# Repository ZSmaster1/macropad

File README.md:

# Macropad

This macropad has 9 keys, an OLED display, a rotary encoder, and 20 individually adressable LEDs for an underglow effect.

## Features
* Two piece PLA case (no screws or heatset inserts necessary!)
* 128x32 OLED display
* EC11 rotary encoder
* 9 keys arranged in a 3x3 matrix
* 20 SK6812MINI-E indvidually adressable LEDs for underglow effects
* Supports QMK, KMK, and more

## Cad Model
The PCB gets sandwiched in between the main body and the bottom piece. The PCB can be glued using the 4 corners onto the main body or foam or some kind of riser can be placed on the protruding columns on the bottom plate. When the bottom plate is glued to the main body the column will snugly fix the PCB in place. This allows the case to stay slim and compact while still allowing the underglow effect to take place.

Made in Fusion 360. Make sure the macropad works outside the case before assembling the case since it will be very hard to take it apart.

## Schematic + PCB
The PCB was made in KiCad, it incorporates 2 layers, a ground plane, and vias.

## Firmware
Currently the firmware is designed to use KMK and circuitpython. However in the future I would like to upgrade to QMK due to its gui configuration interface and more advanced features.

## BOM
Everyting you need to make this macropad:

| Part | Quantity | Optional |
| --- | --- | --- |
| Cherry MX switches | 9 |
| DSA keycaps | 9 |
| 1N4148 DO-35 diode | 9 |
| SK6812MINI-E LED | 20 |
| 0.91" 128x32 i2c OLED Display | 1 |
| EC11 Rotary Encoder | 1 |
| XIAO RP2040 microcontroller | 1 |
| PCB | 1 |
| Case - top | 1 |
| Case - bottom | 1 |
| 100nf through-hole capacitor | 10 | yes

Right now the capacitors were added into the PCB just in case there are any issues with voltage drops due to the amount of LEDs.

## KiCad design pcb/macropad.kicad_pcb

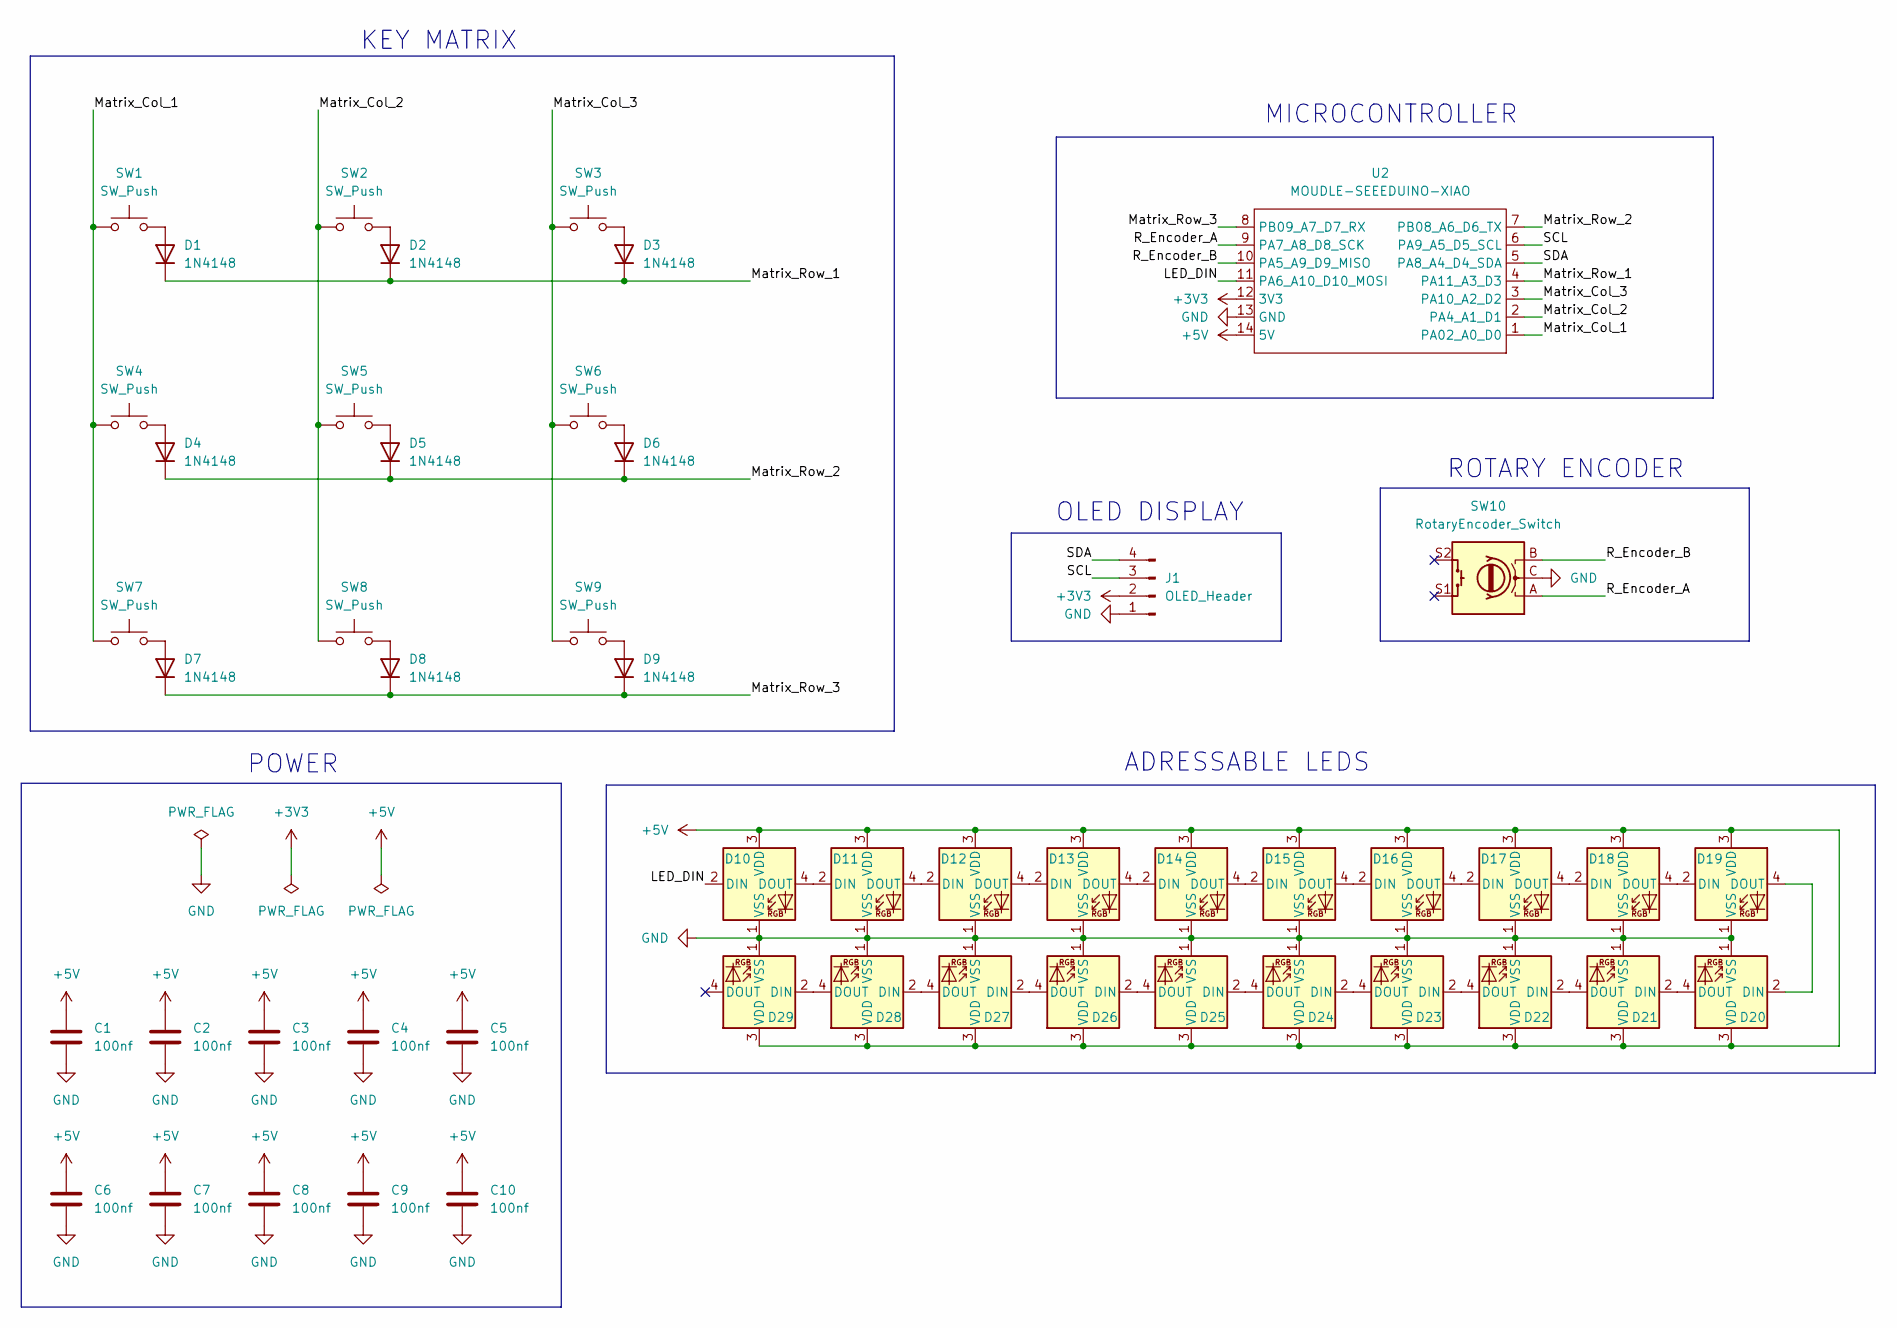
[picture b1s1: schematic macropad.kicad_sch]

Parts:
C1, C2, C3, C4, C5, C6, C7, C8, C9, C10: 100nf; C_Disc_D5.0mm_W2.5mm_P2.50mm
D1, D2, D3, D4, D5, D6, D7, D8, D9: 1N4148; D_DO-35_SOD27_P7.62mm_Horizontal
D10, D11, D12, D13, D14, D15, D16, D17, D18, D19, D20, D21, D22, D23, D24, D25, D26, D27, D28, D29: SK6812MINI-E; LED_SK6812MINI-E_3.2x2.8mm_P1.5mm_ReverseMount
J1: OLED_Header; PinHeader_1x04_P2.54mm_Vertical
SW1, SW2, SW3, SW4, SW5, SW6, SW7, SW8, SW9: SW_Push; SW_Cherry_MX_1.00u_PCB
SW10: RotaryEncoder_Switch; RotaryEncoder_Alps_EC11E-Switch_Vertical_H20mm
U2: MOUDLE-SEEEDUINO-XIAO; XIAO-Generic-Hybrid-14P-2.54-21X17.8MM

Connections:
+3V3: J1.2, U2.12 (3V3)
+5V: C1.1, C2.1, C3.1, C4.1, C5.1, C6.1, C7.1, C8.1, C9.1, C10.1, D10.3 (VDD), D11.3 (VDD), D12.3 (VDD), D13.3 (VDD), D14.3 (VDD), D15.3 (VDD), D16.3 (VDD), D17.3 (VDD), D18.3 (VDD), D19.3 (VDD), D20.3 (VDD), D21.3 (VDD), D22.3 (VDD), D23.3 (VDD), D24.3 (VDD), D25.3 (VDD), D26.3 (VDD), D27.3 (VDD), D28.3 (VDD), D29.3 (VDD), U2.14 (5V)
/LED_DIN: D10.2 (DIN), U2.11 (PA6_A10_D10_MOSI)
/Matrix_Col_1: SW1.1, SW4.1, SW7.1, U2.1 (PA02_A0_D0)
/Matrix_Col_2: SW2.1, SW5.1, SW8.1, U2.2 (PA4_A1_D1)
/Matrix_Col_3: SW3.1, SW6.1, SW9.1, U2.3 (PA10_A2_D2)
/Matrix_Row_1: D1.1 (K), D2.1 (K), D3.1 (K), U2.4 (PA11_A3_D3)
/Matrix_Row_2: D4.1 (K), D5.1 (K), D6.1 (K), U2.7 (PB08_A6_D6_TX)
/Matrix_Row_3: D7.1 (K), D8.1 (K), D9.1 (K), U2.8 (PB09_A7_D7_RX)
/R_Encoder_A: SW10.A, U2.9 (PA7_A8_D8_SCK)
/R_Encoder_B: SW10.B, U2.10 (PA5_A9_D9_MISO)
/SCL: J1.3, U2.6 (PA9_A5_D5_SCL)
/SDA: J1.4, U2.5 (PA8_A4_D4_SDA)
GND: C1.2, C2.2, C3.2, C4.2, C5.2, C6.2, C7.2, C8.2, C9.2, C10.2, D10.1 (VSS), D11.1 (VSS), D12.1 (VSS), D13.1 (VSS), D14.1 (VSS), D15.1 (VSS), D16.1 (VSS), D17.1 (VSS), D18.1 (VSS), D19.1 (VSS), D20.1 (VSS), D21.1 (VSS), D22.1 (VSS), D23.1 (VSS), D24.1 (VSS), D25.1 (VSS), D26.1 (VSS), D27.1 (VSS), D28.1 (VSS), D29.1 (VSS), J1.1, SW10.C, U2.13 (GND)
unnamed: D1.2 (A), SW1.2
unnamed: D2.2 (A), SW2.2
unnamed: D3.2 (A), SW3.2
unnamed: D4.2 (A), SW4.2
unnamed: D5.2 (A), SW5.2
unnamed: D6.2 (A), SW6.2
unnamed: D7.2 (A), SW7.2
unnamed: D8.2 (A), SW8.2
unnamed: D9.2 (A), SW9.2
unnamed: D10.4 (DOUT), D11.2 (DIN)
unnamed: D11.4 (DOUT), D12.2 (DIN)
unnamed: D12.4 (DOUT), D13.2 (DIN)
unnamed: D13.4 (DOUT), D14.2 (DIN)
unnamed: D14.4 (DOUT), D15.2 (DIN)
unnamed: D15.4 (DOUT), D16.2 (DIN)
unnamed: D16.4 (DOUT), D17.2 (DIN)
unnamed: D17.4 (DOUT), D18.2 (DIN)
unnamed: D18.4 (DOUT), D19.2 (DIN)
unnamed: D19.4 (DOUT), D20.2 (DIN)
unnamed: D20.4 (DOUT), D21.2 (DIN)
unnamed: D21.4 (DOUT), D22.2 (DIN)
unnamed: D22.4 (DOUT), D23.2 (DIN)
unnamed: D23.4 (DOUT), D24.2 (DIN)
unnamed: D24.4 (DOUT), D25.2 (DIN)
unnamed: D25.4 (DOUT), D26.2 (DIN)
unnamed: D26.4 (DOUT), D27.2 (DIN)
unnamed: D27.4 (DOUT), D28.2 (DIN)
unnamed: D28.4 (DOUT), D29.2 (DIN)

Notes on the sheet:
KEY MATRIX
OLED DISPLAY
MICROCONTROLLER
ADRESSABLE LEDS
ROTARY ENCODER
POWER

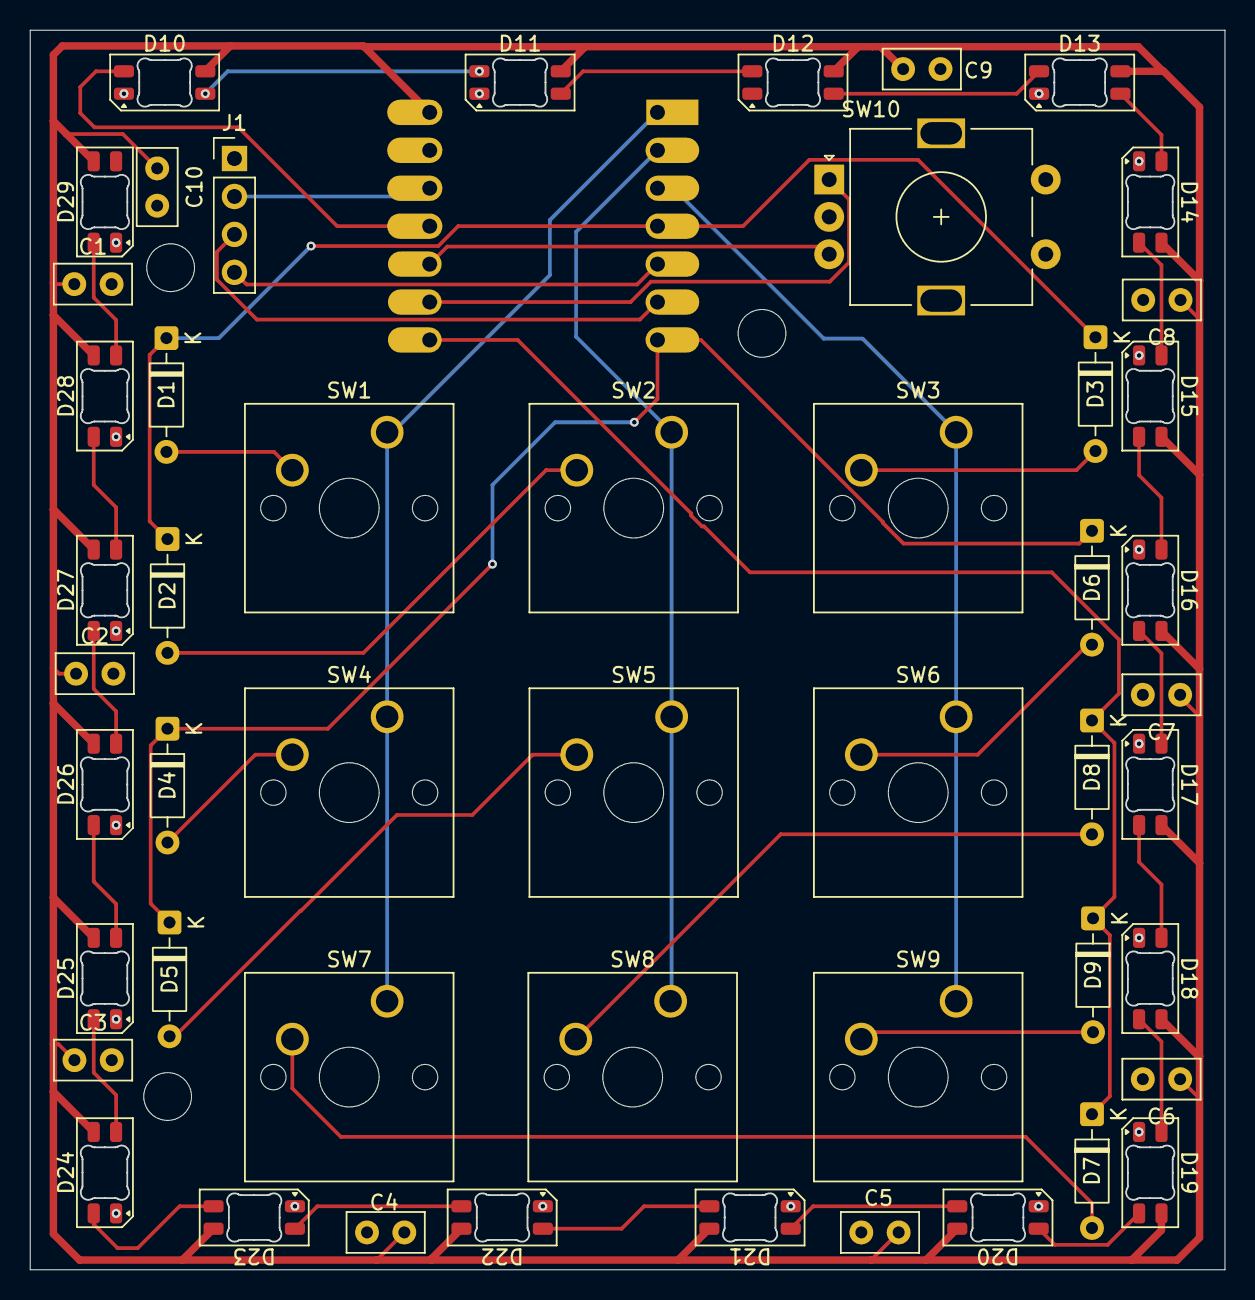
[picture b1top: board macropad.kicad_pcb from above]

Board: 2 copper layers, 80.0 x 83.0 mm, 51 parts (1 on the bottom side), 42 nets.

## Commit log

2026-06-09 Rename bottom.step to production/bottom.step
2026-06-09 Rename main body.step to production/main body.step
2026-06-09 Rename macropad_rev1.step to cad/macropad_rev1.step
2026-06-09 Rename main.py to firmware/kmk/main.py
2026-06-09 Rename main.py to production/main.py
2026-06-09 Rename gerbers.zip to production/gerbers.zip
2026-06-09 Enhance README with project details and specifications
    Expanded README with detailed features, CAD model, schematic, firmware, and BOM.
2026-06-09 Update README with assembly note for macropad
    Added a note about testing the macropad before assembly.
2026-06-11 Add demo.md with links to CAD and PCB models
2026-06-27 Add bill of materials for project components
2026-06-27 Fix formatting of 100nf capacitor entry in bom.csv
2026-06-27 Fix formatting issues in bom.csv
